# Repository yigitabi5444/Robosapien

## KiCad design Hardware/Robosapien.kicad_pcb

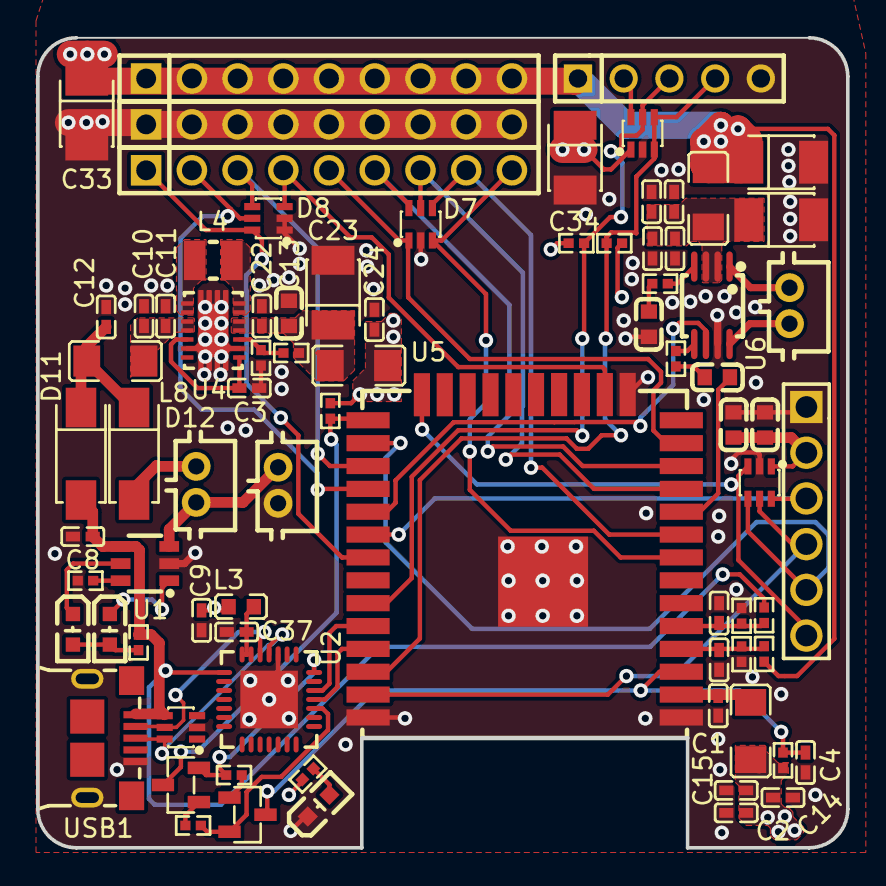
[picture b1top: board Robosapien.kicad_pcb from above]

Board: 4 copper layers, 45.0 x 45.0 mm, 79 parts (0 on the bottom side), 55 nets.

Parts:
C1, C24, C25, C26, C37: 100nF; C0402_NEW
C2, C4, C10, C11, C12, C14, C15, C22: 10uF; C0402
C3, C28, C30: 16V 100nF X7R ±10% 0402; C0402_NEW
C8, C19, C31: 25V 1uF X5R ±10% 0402; C0402
C9: 1uF; C0402
C13, C29, C32: 22uF; C0603
C17, C27: 100uF 6.3V Tantal 3528; CAP-SMD_L3.5-W2.8
C18, C20: 15nF; C0603
C23, C33, C34: 100uF; CAP-SMD_L3.5-W2.8
CN1, CN2, CN3: B2B-PH-K-S(LF)(SN); CONN-TH_B2B-PH-K-S
D1, D4, D5, D7, D8: SMF05CT1G; SOT-363_L2.0-W1.3-P0.65-LS2.1-BR
D11, D12: SS14; SMA_L4.2-W2.6-LS5.3-RD
H1, H2, H6: 9P 2.54 Male Header; HDR-TH_9P-P2.54-V-M
H3: 6P 2.54 Male Header; HDR-TH_6P-P2.54-V-M-1
H8: Header 2.54 5P Female; HDR-TH_5P-P2.54-V-F
L1, L5, L6, L8: 120Ω 3A; L1206
L3: 600Ω 200mA; L0603
L4: 2.8A 1uH ±20% 45mΩ; IND-SMD_L2.5-W2.0
LED1: Red LED 0603; LED0603-R-RD
LED2: Green LED 0603; LED0603-R-RD
LED3: White Led 0603; LED0603-R-RD_WHITE
Q1, Q2: SS8050_C2150; SOT-23-3_L2.9-W1.3-P1.90-LS2.4-BR
R1, R3, R5, R10, R11, R12, R13, R17, R18, R19: 10kΩ 0402 50V; R0402
R2: 100kΩ 0402 50V; R0402
R4: 2kΩ 0402 50V; R0402
R7: 1kΩ 0402 50V; R0402
R8: 18kΩ 0402 50V; R0402
R14, R15: 150kΩ 0402 50V; R0402
R25: 4.7kΩ 0402 50V; R0402
U1: TP4057; SOT-23-6_L2.9-W1.6-P0.95-LS2.8-BR
U2: CP2102-GMR; WQFN-28_L5.0-W5.0-P0.50-BL-EP3.2
U4: TPS63020DSJR; VSON-14_L4.0-W3.0-P0.50-BL-EP_TI_DSJ
U5: ESP32-WROOM-32D(8MB); WIFIM-SMD_39P-L25.5-W18.0-P1.27
U6: PAM8303DBSC; MSOP-8_L3.0-W3.0-P0.65-LS5.0-BL
USB1: 10118193-0001LF; MICRO-USB-SMD_10118193-0001LF

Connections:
+3.3V: C2.2, C9.2, C14.2, C15.2, C24.2, C29.2, C32.2, D4.1, D5.6, H3.2, H8.2, L1.1, L3.1, L5.1, R1.2, R13.1, R17.1, R18.1, R25.2
+BATT: C17.1, C33.1, C34.1, CN3.2, D5.1, D12.2 (A), H1.1, H1.2, H1.3, H1.4, H1.5, H1.6, H1.7, H1.8, H1.9, H8.1, L6.1, R11.2
/Audio: C18.1, U5.10 (IO25)
/Audio Amplifier/Speaker+: CN2.2, U6.1 (OUT+)
/Audio Amplifier/Speaker-: CN2.1, U6.8 (OUT-)
/Audio_Enable: U5.29 (IO5), U6.6 (~SD)
/BMS/BAT+: CN1.2, CN3.1, U1.3 (BAT)
/ESP_EN: C4.2, Q1.3 (C), R13.2, U5.3 (EN)
/ESP_IO0: Q2.3 (C), R1.1, U5.25 (IO0)
/ESP_RX: U2.26 (TXD), U5.34 (RXD0)
/ESP_TX: U2.25 (RXD), U5.35 (TXD0)
/Esp32/IO36: C26.2, R11.1, R12.2, U5.4 (SENSOR_VP)
/Esp32/IO39: C25.2, R10.1, R19.2, U5.5 (SENSOR_VN)
/SCL: D5.3, D5.4, H8.4, R17.2, U5.36 (IO22)
/SDA: D5.5, H8.3, R18.2, U5.33 (IO21)
/SERVO1: D8.6, H2.1, U5.31 (IO19)
/SERVO2: D8.5, H2.2, U5.28 (IO17)
/SERVO3: D8.4, H2.3, U5.27 (IO16)
/SERVO4: D8.3, H2.4, U5.16 (IO13)
/SERVO5: D7.1, H2.5, U5.13 (IO14)
/SERVO6: D7.6, H2.6, U5.12 (IO27)
/SERVO7: D7.5, H2.7, U5.11 (IO26)
/SERVO8: D7.4, H2.8, U5.9 (IO33)
/SERVO9: D7.3, H2.9, U5.8 (IO32)
/Screen1: D4.6, H3.3, U5.30 (IO18)
/Screen2: D4.5, H3.4, U5.37 (IO23)
/Screen3: D4.4, H3.5, U5.26 (IO4)
/Screen4: D4.3, H3.6, U5.24 (IO2)
/USB_CP2102/D+: D1.6, U2.4 (D+), USB1.3 (Data+)
/USB_CP2102/D-: D1.5, U2.5 (D-), USB1.2 (Data-)
/USB_CP2102/DTR: Q2.2 (E), R3.1, U2.28 (DTR)
/USB_CP2102/RTS: Q1.2 (E), R5.1, U2.24 (RTS)
/VBUS: C8.2, D1.4, D11.2 (A), R7.2, R10.2, U1.4 (VCC), U2.8 (VBUS), USB1.1 (VBUS)
GND: C1.1, C2.1, C3.1, C4.1, C8.1, C9.1, C10.1, C11.1, C12.1, C13.1, C14.1, C15.1, C17.2, C19.1, C20.1, C22.1, C23.2, C24.1, C25.1, C26.1, C27.2, C28.1, C29.1, C30.1, C31.1, C32.1, C33.2, C34.2, C37.1, CN1.1, D1.2, D4.2, D5.2, D7.2, D8.1, D8.2, H3.1, H6.1, H6.2, H6.3, H6.4, H6.5, H6.6, H6.7, H6.8, H6.9, H8.5, LED3.2 (K), R4.1, R8.1, R12.1, R19.1, U1.2 (GND), U2.3 (GND), U2.29 (EP), U4.2 (GND), U4.13 (PS/SYNC), U4.15 (PGND), U5.1 (GND), U5.15 (GND), U5.38 (GND), U5.39 (GND), U6.7 (GND), USB1.5 (GND), USB1.6 (S)
unnamed: C10.2, C11.2, L8.1, U4.10 (VIN), U4.11 (VIN)
unnamed: C13.2, C22.2, C23.1, L1.2, R2.2, U4.4 (VOUT), U4.5 (VOUT)
unnamed: C18.2, R15.1
unnamed: C20.2, R14.1
unnamed: C12.2, D11.1 (K), D12.1 (K), L8.2
unnamed: L4.1, U4.8 (L1), U4.9 (L1)
unnamed: L4.2, U4.6 (L2), U4.7 (L2)
unnamed: LED1.1 (A), LED2.1 (A), R7.1
unnamed: LED1.2 (K), U1.1 (CHRG)
unnamed: LED2.2 (C), U1.5 (STDBY)
unnamed: LED3.1 (A), R25.1
unnamed: Q1.1 (B), R3.2
unnamed: Q2.1 (B), R5.2
unnamed: R4.2, U1.6 (PROG)
unnamed: C37.2, L3.2, U2.6 (VDD), U2.7 (REGIN)
unnamed: C3.2, U4.1 (VINA), U4.12 (EN)
unnamed: R2.1, R8.2, U4.3 (FB)
unnamed: C1.2, L5.2, U5.2 (VDD33)
unnamed: R15.2, U6.5 (IN+)
unnamed: R14.2, U6.4 (IN-)
unnamed: C19.2, C27.1, C28.2, C30.2, C31.2, L6.2, U6.2 (PVDD), U6.3 (VDD)

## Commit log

2023-02-11 Added esp32 and bms
2023-02-16 New pcb
2023-03-06 V2 Board
2023-04-03 asas
2023-05-09 Servo test code ready
2023-07-21 PCB V2
2023-08-20 dasd
2023-08-20 adsads
2023-12-26 Refactor code and remove unused zoom functionality
